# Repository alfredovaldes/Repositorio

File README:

Eagle files for an several PCBs

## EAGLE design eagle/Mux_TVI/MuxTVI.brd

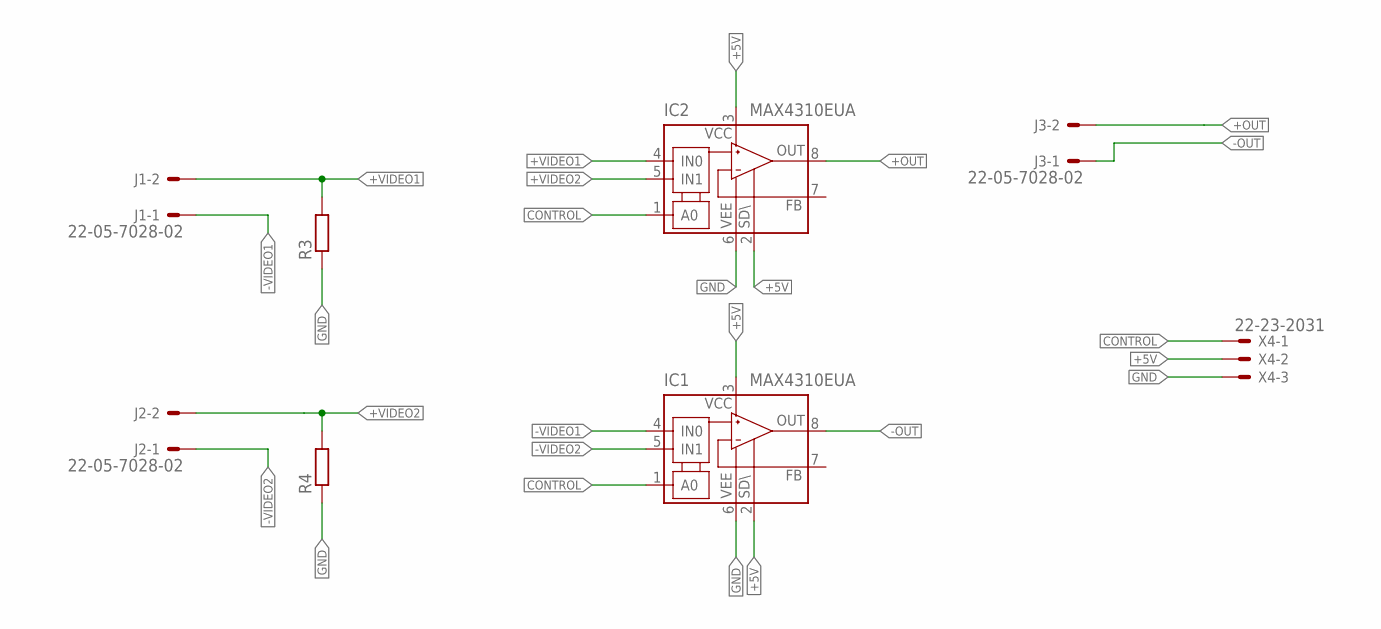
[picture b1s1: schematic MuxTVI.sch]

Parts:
IC1, IC2: MAX4310EUA; SO08
J1, J2, J3: 22-05-7028-02; 7395-02
R3, R4: R-EU_R1206; R1206
X4: 22-23-2031

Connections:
+5V: IC1.2 (!SHDN), IC1.3 (V+), IC2.2 (!SHDN), IC2.3 (V+), X4.2
+OUT: IC2.8 (OUT), J3.2
+VIDEO1: IC2.4 (IN0), J1.2, R3.2
+VIDEO2: IC2.5 (IN1), J2.2, R4.2
-OUT: IC1.8 (OUT), J3.1
-VIDEO1: IC1.4 (IN0), J1.1
-VIDEO2: IC1.5 (IN1), J2.1
CONTROL: IC1.1 (A0), IC2.1 (A0), X4.1
FB: IC1.7 (FB), IC2.7 (FB)
GND: IC1.6 (V-), IC2.6 (V-), R3.1, R4.1, X4.3

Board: 2 copper layers, 8 parts (0 on the bottom side), 10 nets, no tracks yet.

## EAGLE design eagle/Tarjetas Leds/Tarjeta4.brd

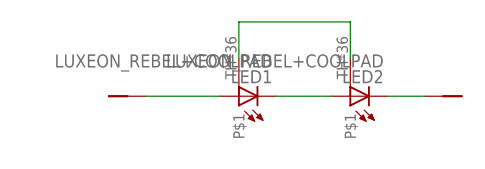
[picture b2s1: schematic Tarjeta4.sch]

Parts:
LED1, LED2: LUXEON_REBEL+COOLPAD
U$1, U$2: POWER_PIN

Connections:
unnamed: LED1.A, LED1.A@1 (A), U$1.P$1
unnamed: LED1.C, LED1.C@1 (C), LED2.A, LED2.A@1 (A)
unnamed: LED2.C, LED2.C@1 (C), U$2.P$1
unnamed: LED1.TH, LED1.TH@1, LED1.TH@2, LED1.TH@3, LED1.TH@4, LED1.TH@5, LED1.TH@6, LED1.TH@7, LED1.TH@8, LED1.TH@9, LED1.TH@10, LED1.TH@11, LED1.TH@12, LED1.TH@13, LED1.TH@14, LED1.TH@15, LED1.TH@16, LED1.TH@17, LED1.TH@18, LED1.TH@19, LED1.TH@20, LED1.TH@21, LED1.TH@22, LED1.TH@23, LED1.TH@24, LED1.TH@25, LED1.TH@26, LED1.TH@27, LED1.TH@28, LED1.TH@29, LED1.TH@30, LED1.TH@31, LED1.TH@32, LED1.TH@33, LED1.TH@34, LED1.TH@35, LED2.TH, LED2.TH@1, LED2.TH@2, LED2.TH@3, LED2.TH@4, LED2.TH@5, LED2.TH@6, LED2.TH@7, LED2.TH@8, LED2.TH@9, LED2.TH@10, LED2.TH@11, LED2.TH@12, LED2.TH@13, LED2.TH@14, LED2.TH@15, LED2.TH@16, LED2.TH@17, LED2.TH@18, LED2.TH@19, LED2.TH@20, LED2.TH@21, LED2.TH@22, LED2.TH@23, LED2.TH@24, LED2.TH@25, LED2.TH@26, LED2.TH@27, LED2.TH@28, LED2.TH@29, LED2.TH@30, LED2.TH@31, LED2.TH@32, LED2.TH@33, LED2.TH@34, LED2.TH@35

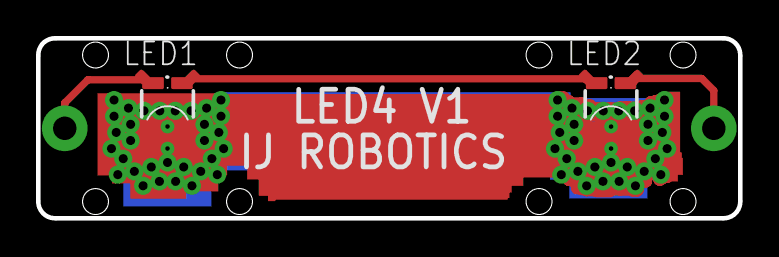
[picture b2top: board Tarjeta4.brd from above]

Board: 2 copper layers, 39.0 x 10.0 mm, 4 parts (0 on the bottom side), 4 nets.

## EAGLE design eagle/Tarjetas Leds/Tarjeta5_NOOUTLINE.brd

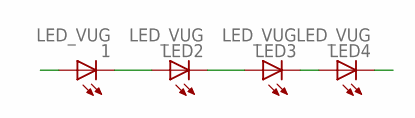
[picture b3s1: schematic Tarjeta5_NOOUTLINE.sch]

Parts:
1: LED_VUG; CINVESTAV_LUXEON
LED2, LED3, LED4: LED_VUG; CINVESTAV_LUXEON

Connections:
GROUND: LED4.C
unnamed: 1.C, LED2.A
unnamed: LED2.C, LED3.A
unnamed: LED3.C, LED4.A
POWER: 1.A

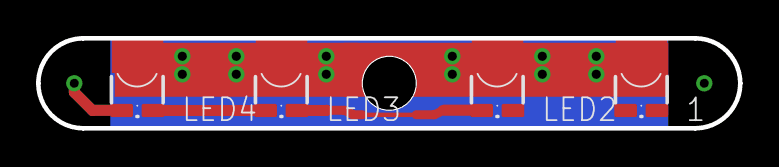
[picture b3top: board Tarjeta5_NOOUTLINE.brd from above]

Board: 2 copper layers, 39.0 x 5.0 mm, 4 parts (0 on the bottom side), 3 nets.

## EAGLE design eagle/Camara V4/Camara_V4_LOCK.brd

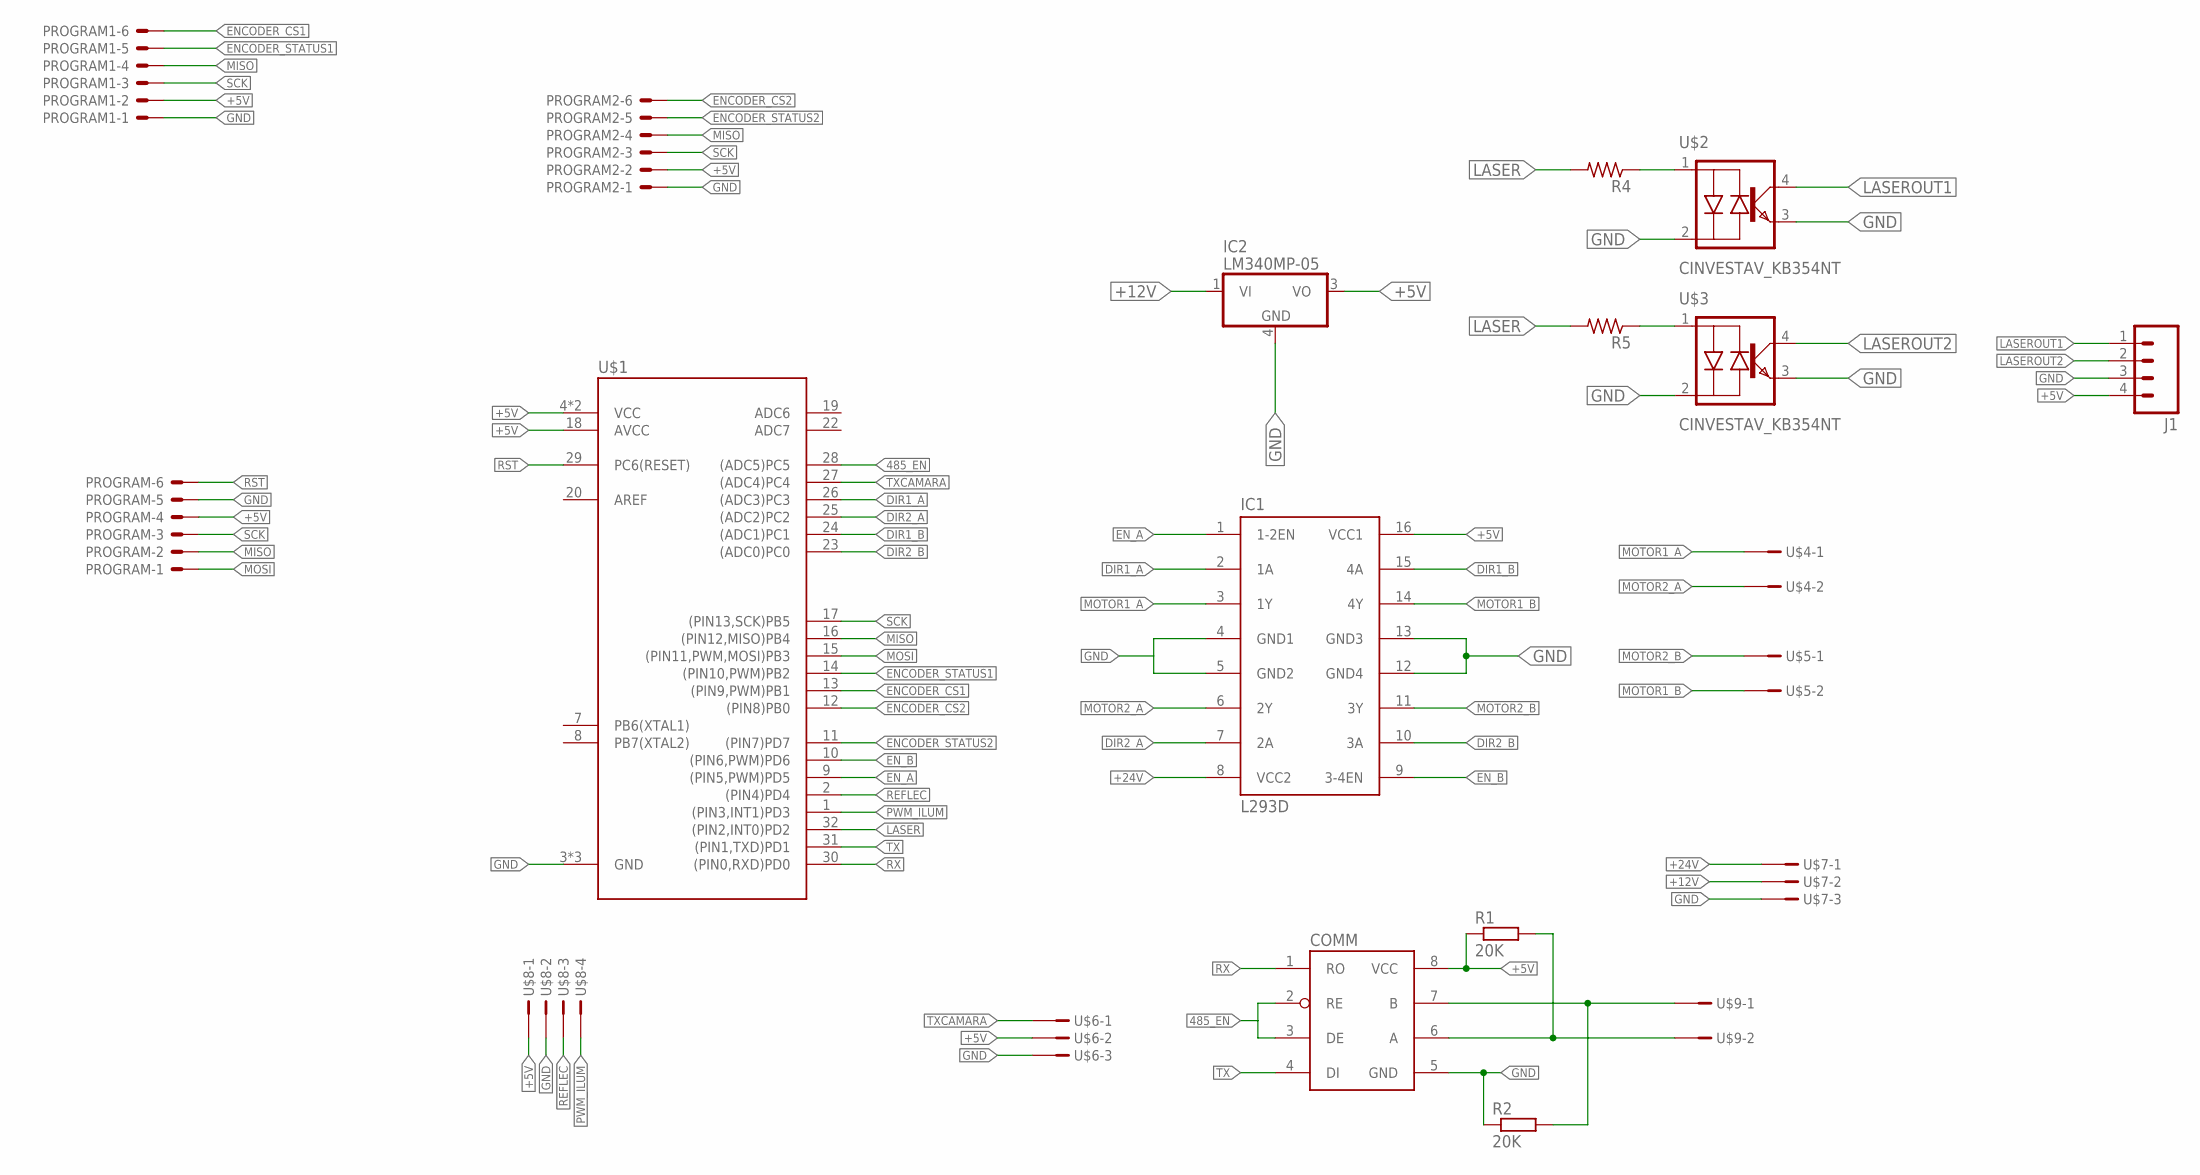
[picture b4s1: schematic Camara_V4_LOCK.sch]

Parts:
COMM: CINVESTAV_ADM1485; CINVESTAV_SOIC8
IC1: L293D; DIL16
IC2: LM340MP-05; SOT223
J1: M04JST-PTH-VERT; JST-4-PTH-VERT
PROGRAM, PROGRAM1, PROGRAM2: 22-23-2061
R1, R2: 20K; R1206
R4, R5: R-US_M1206; M1206
U$1: CINVESTAV_ATMEGA328; CINVESTAV_TQFP32-08
U$2, U$3: CINVESTAV_KB354NT; CINVESTAV_SOIC4
U$4, U$5, U$9: XH-02
U$6, U$7: XH-03
U$8: XH-04

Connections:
485_EN: COMM.2 (RE), COMM.3 (DE), U$1.28 ((ADC5)PC5)
+5V: COMM.8 (VCC), IC1.16 (VCC1), IC2.3 (VO), J1.4, PROGRAM.4, PROGRAM1.2, PROGRAM2.2, R1.1, U$1.4 (VCC), U$1.6 (VCC), U$1.18 (AVCC), U$6.P$2, U$8.P$1
+12V: IC2.1 (VI), U$7.P$2
+24V: IC1.8 (VCC2), U$7.P$1
DIR1_A: IC1.2 (1A), U$1.26 ((ADC3)PC3)
DIR1_B: IC1.15 (4A), U$1.24 ((ADC1)PC1)
DIR2_A: IC1.7 (2A), U$1.25 ((ADC2)PC2)
DIR2_B: IC1.10 (3A), U$1.23 ((ADC0)PC0)
ENCODER_CS1: PROGRAM1.6, U$1.13 ((PIN9,PWM)PB1)
ENCODER_CS2: PROGRAM2.6, U$1.12 ((PIN8)PB0)
ENCODER_STATUS1: PROGRAM1.5, U$1.14 ((PIN10,PWM)PB2)
ENCODER_STATUS2: PROGRAM2.5, U$1.11 ((PIN7)PD7)
EN_A: IC1.1 (1-2EN), U$1.9 ((PIN5,PWM)PD5)
EN_B: IC1.9 (3-4EN), U$1.10 ((PIN6,PWM)PD6)
GND: COMM.5 (GND), IC1.4 (GND1), IC1.5 (GND2), IC1.12 (GND4), IC1.13 (GND3), IC2.4 (GND), J1.3, PROGRAM.5, PROGRAM1.1, PROGRAM2.1, R2.1, U$1.3 (GND), U$1.5 (GND), U$1.21 (GND), U$2.2 (C/A), U$2.3 (EMIT), U$3.2 (C/A), U$3.3 (EMIT), U$6.P$3, U$7.P$3, U$8.P$2
LASER: R4.2, R5.2, U$1.32 ((PIN2,INT0)PD2)
LASEROUT1: J1.1, U$2.4 (COL)
LASEROUT2: J1.2, U$3.4 (COL)
MISO: PROGRAM.2, PROGRAM1.4, PROGRAM2.4, U$1.16 ((PIN12,MISO)PB4)
MOSI: PROGRAM.1, U$1.15 ((PIN11,PWM,MOSI)PB3)
MOTOR1_A: IC1.3 (1Y), U$4.P$1
MOTOR1_B: IC1.14 (4Y), U$5.P$2
MOTOR2_A: IC1.6 (2Y), U$4.P$2
MOTOR2_B: IC1.11 (3Y), U$5.P$1
unnamed: R4.1, U$2.1 (A/C)
unnamed: COMM.6 (A), R1.2, U$9.P$2
unnamed: COMM.7 (B), R2.2, U$9.P$1
unnamed: R5.1, U$3.1 (A/C)
PWM_ILUM: U$1.1 ((PIN3,INT1)PD3), U$8.P$4
REFLEC: U$1.2 ((PIN4)PD4), U$8.P$3
RST: PROGRAM.6, U$1.29 (PC6(RESET))
RX: COMM.1 (RO), U$1.30 ((PIN0,RXD)PD0)
SCK: PROGRAM.3, PROGRAM1.3, PROGRAM2.3, U$1.17 ((PIN13,SCK)PB5)
TX: COMM.4 (DI), U$1.31 ((PIN1,TXD)PD1)
TXCAMARA: U$1.27 ((ADC4)PC4), U$6.P$1

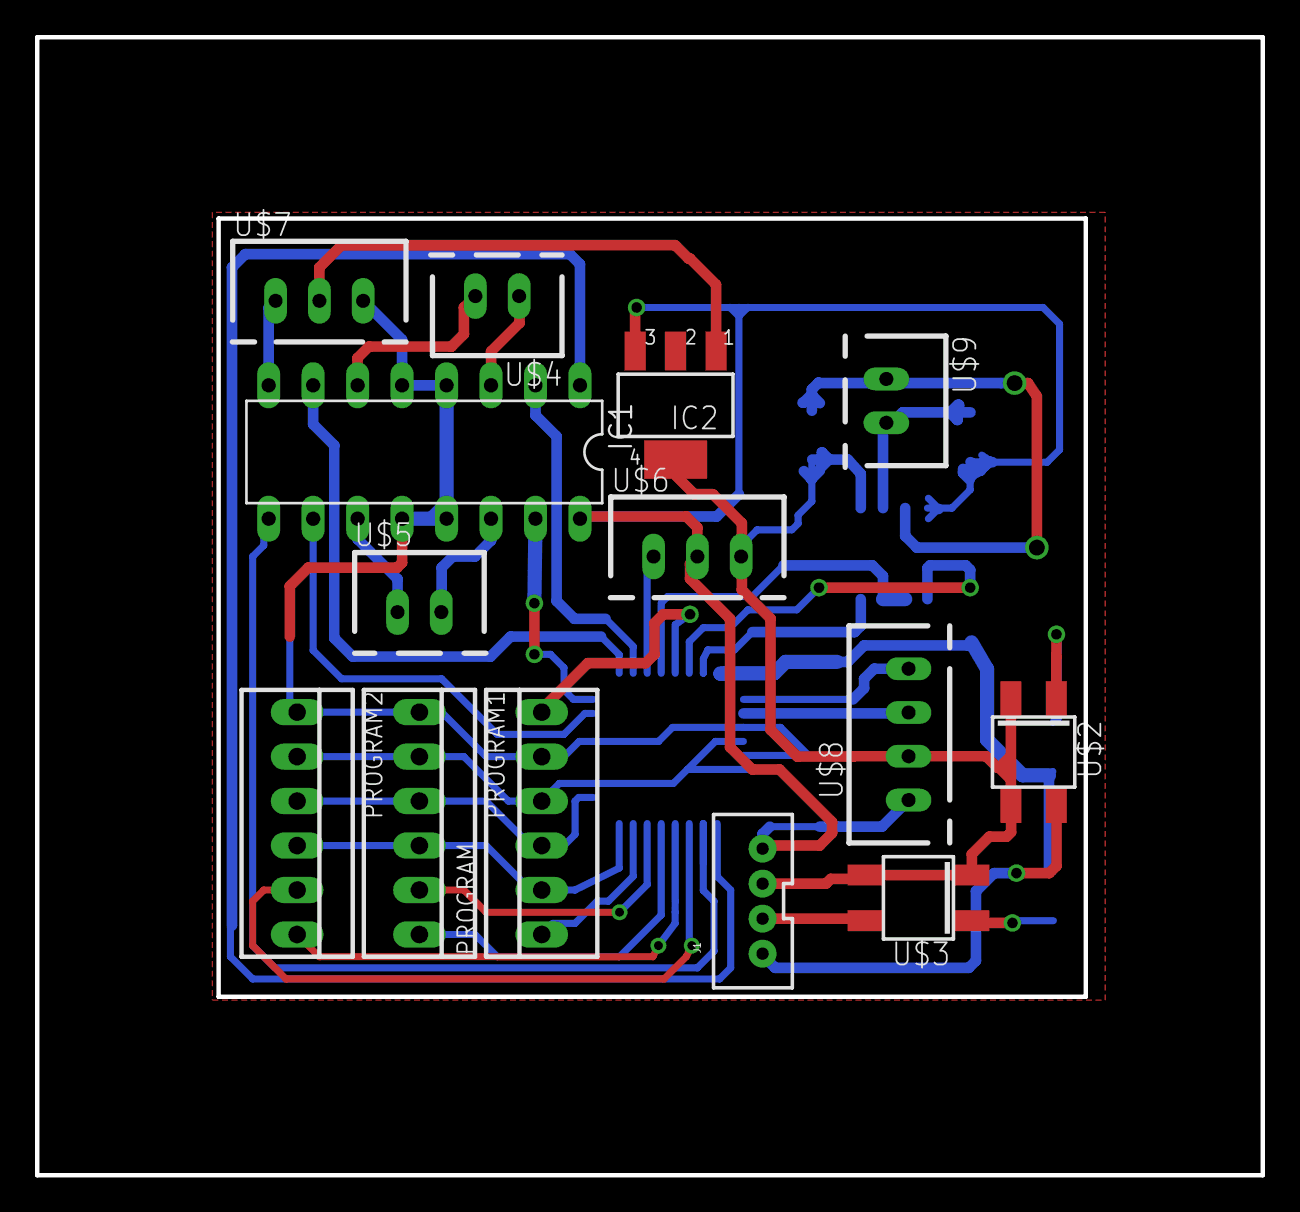
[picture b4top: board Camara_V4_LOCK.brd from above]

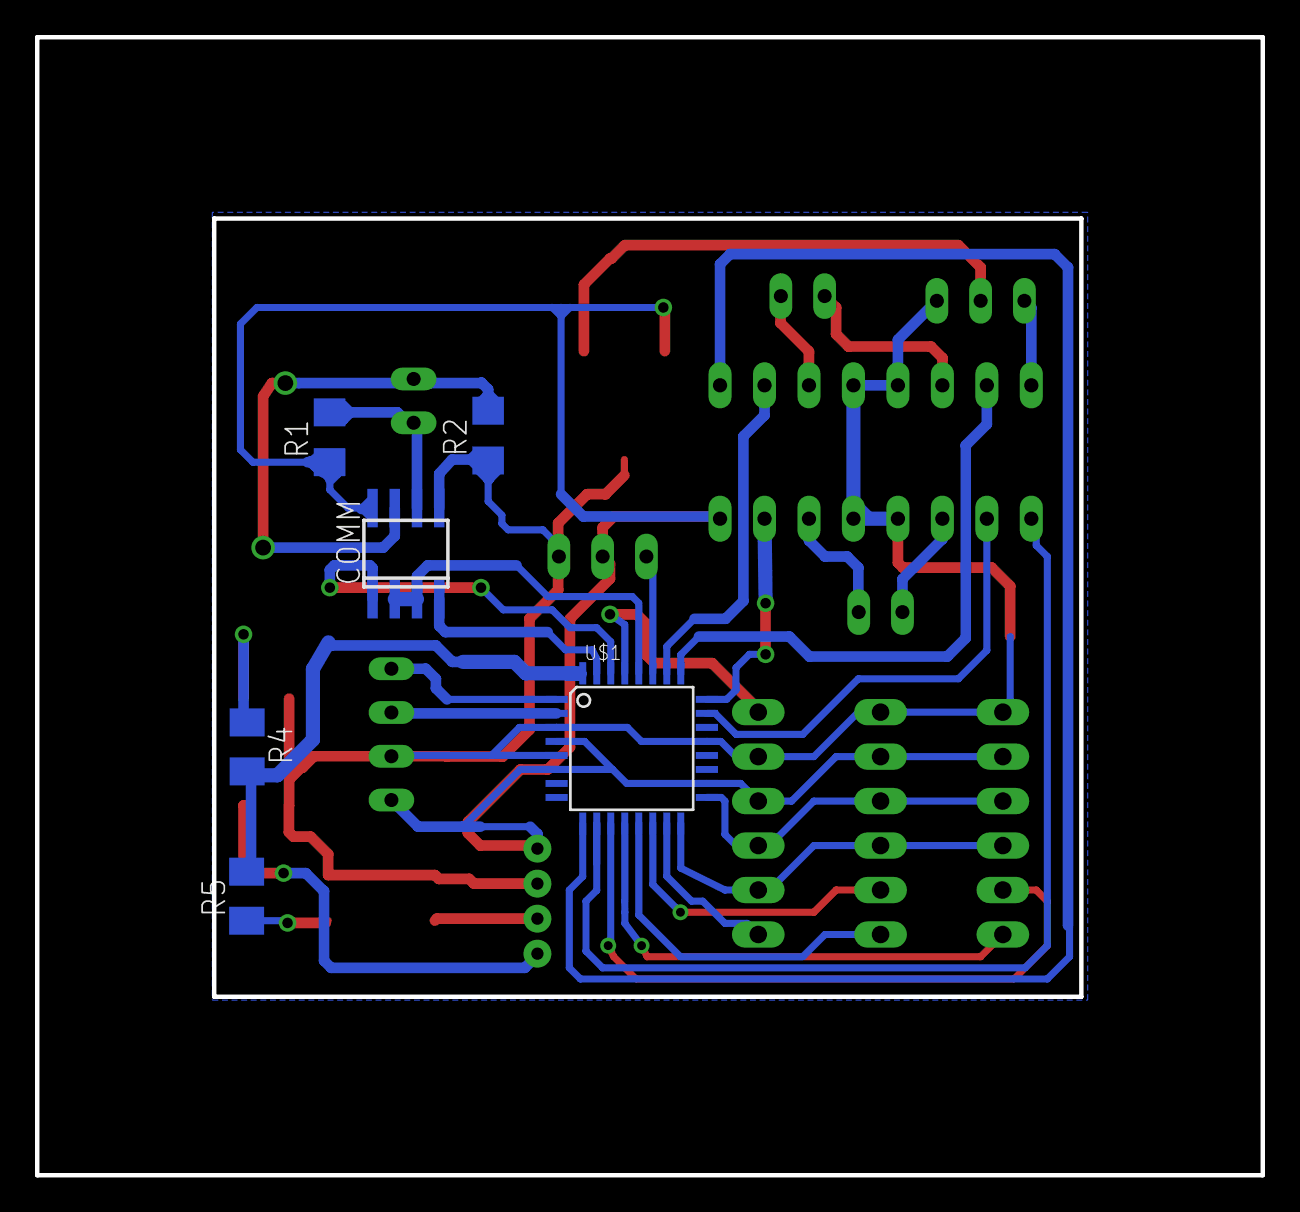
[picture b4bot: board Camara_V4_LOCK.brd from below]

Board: 2 copper layers, 70.0 x 65.0 mm, 20 parts (6 on the bottom side), 35 nets.

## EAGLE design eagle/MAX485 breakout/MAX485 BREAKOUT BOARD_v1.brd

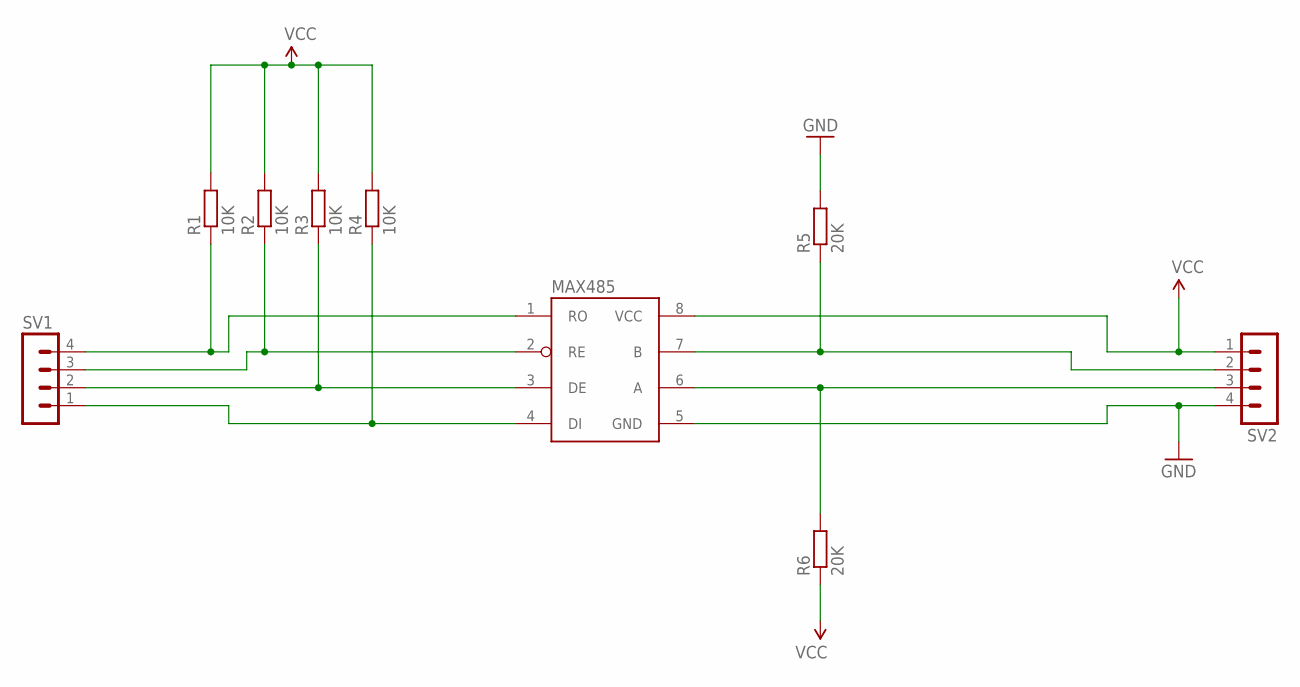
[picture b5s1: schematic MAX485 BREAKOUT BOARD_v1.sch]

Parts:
MAX485: CINVESTAV_ADM1485; CINVESTAV_SOIC8
R1, R2, R3, R4: 10K; RCL_R1206
R5, R6: 20K; RCL_R1206
SV1, SV2: MA04-1

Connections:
GND: MAX485.5 (GND), R5.2, SV2.4
unnamed: MAX485.1 (RO), R1.1, SV1.4
unnamed: MAX485.2 (RE), R2.1, SV1.3
unnamed: MAX485.3 (DE), R3.1, SV1.2
unnamed: MAX485.4 (DI), R4.1, SV1.1
unnamed: MAX485.6 (A), R6.2, SV2.3
unnamed: MAX485.7 (B), R5.1, SV2.2
VCC: MAX485.8 (VCC), R1.2, R2.2, R3.2, R4.2, R6.1, SV2.1

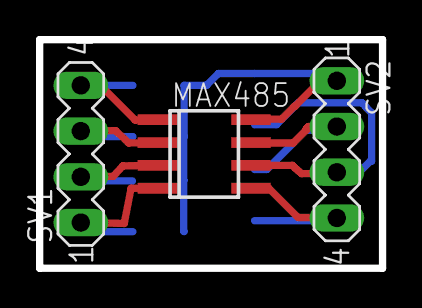
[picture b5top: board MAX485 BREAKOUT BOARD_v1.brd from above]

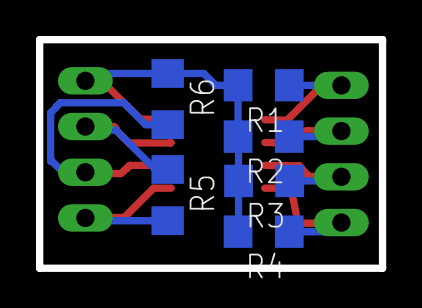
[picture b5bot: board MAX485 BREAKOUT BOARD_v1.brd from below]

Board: 2 copper layers, 19.1 x 12.7 mm, 9 parts (6 on the bottom side), 8 nets.

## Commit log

2016-02-25 prueba 1
2016-10-11 Incluyo PCBs

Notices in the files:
parts and their libraries:
SparkFun-Connectors: Licensing: Creative Commons ShareAlike 4.0 International - https://creativecommons.org/licenses/by-sa/4.0
